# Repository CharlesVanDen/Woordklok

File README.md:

# Woordklok
Alternatieve besturing voor de woordklok van Samenkopen 2016
Dit project bestaat uit:
* een pcb met daarop een ATMEGA en andere elektronica
* een ESP01
* software voor de ATMEGA (Atmel Studio)
* software voor de ESP (Arduino)

Klik op Wiki (hierboven) voor meer informatie

CONTACT: Klik op Wiki (hierboven) en daarna op Bestellen

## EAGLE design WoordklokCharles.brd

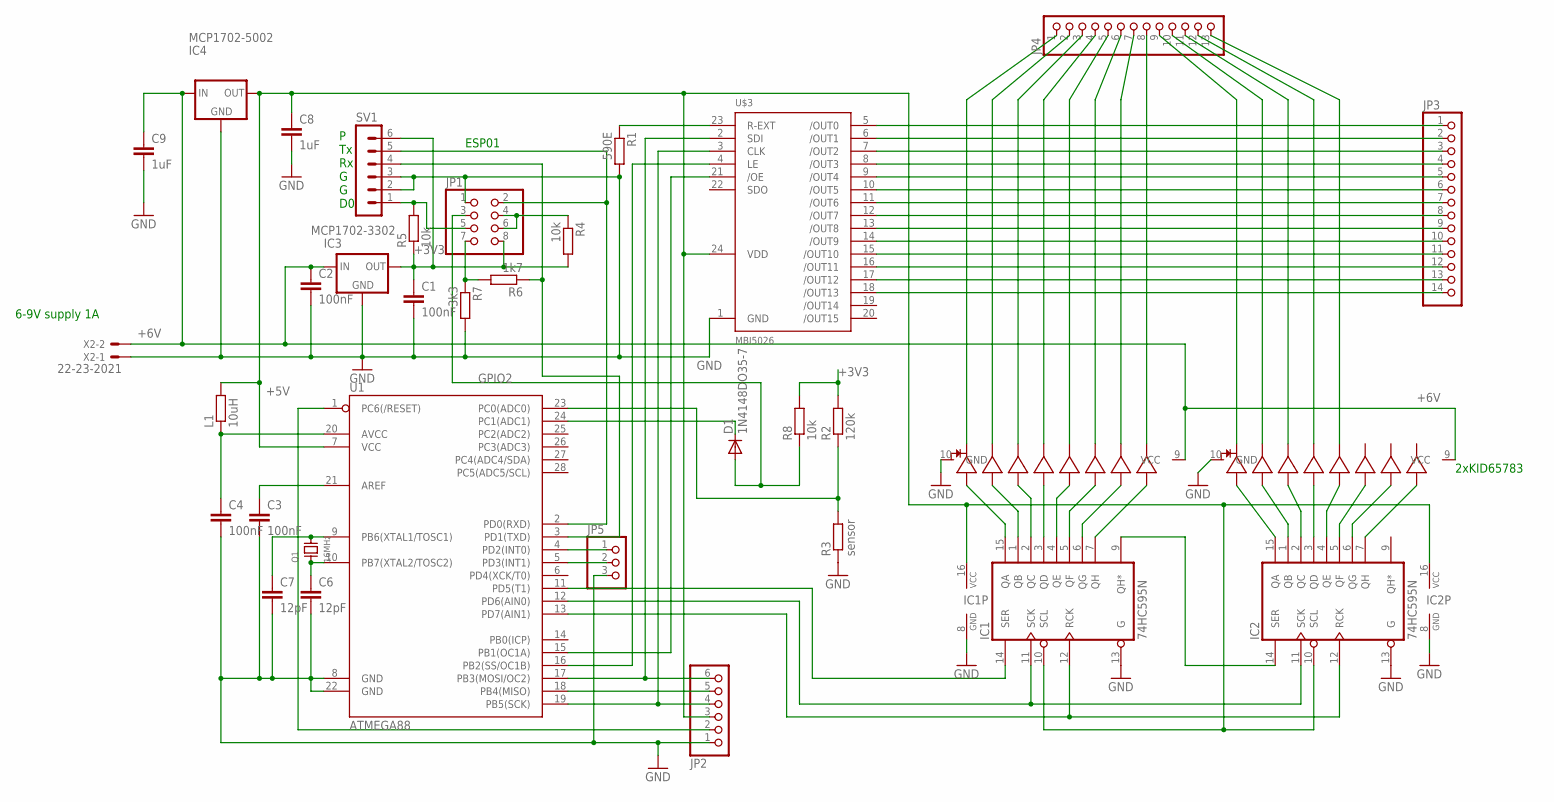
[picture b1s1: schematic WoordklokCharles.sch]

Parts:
C1, C2, C3, C4: 100nF; C025-024X044
C6, C7: 12pF; C025-024X044
C8, C9: 1uF; C025-024X044
D1: 1N4148DO35-7; DO35-7
IC1, IC2: 74HC595N; DIL16
IC3: MCP1702-3302; TO92
IC4: MCP1702-5002; TO92
JP1: PINHD-2X4; 2X04
JP2: PINHD-1X6; 1X06
JP3: PINHD-1X14; 1X14
JP4: PINHD-1X13; 1X13
JP5: PINHD-1X3; 1X03
L1: 10uH; 0204/7
Q1: 16MHz; XTAL
R1: 590E; 0204/7
R2: 120k; 0204/7
R3: sensor; 0204/7
R4, R5: 10k; 0204V
R6: 1k7; 0204/7
R7: 3k3; 0204/7
R8: 10k; 0204/7
SV1: MA06-1
U1: ATMEGA88; DIL28-3
U$1, U$2: KID65783; DIP18
U$3: MBI5026; DIP24
X2: 22-23-2021

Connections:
+3V3: C1.1, IC3.3 (OUT), JP1.8, R2.2, R4.2, R5.1, R8.2, SV1.6
+5V: C8.1, IC1.10 (SCL), IC1.16 (VCC), IC2.10 (SCL), IC2.16 (VCC), IC4.3 (OUT), JP2.3, L1.2, U1.7 (VCC), U$3.24 (VDD)
+6V: C2.1, C9.1, IC3.2 (IN), IC4.2 (IN), U$1.9 (VCC), U$2.9 (VCC), X2.2
AVCC: C4.1, L1.1, U1.20 (AVCC)
ESP2: JP1.2, SV1.5, U1.2 (PD0(RXD))
ESP7: R6.1, SV1.4, U1.3 (PD1(TXD))
GND: C1.2, C2.2, C3.2, C4.2, C6.2, C7.2, C8.2, C9.2, IC1.8 (GND), IC1.13 (G), IC2.8 (GND), IC2.13 (G), IC3.1 (GND), IC4.1 (GND), JP1.1, JP2.1, JP5.3, R1.2, R3.1, R7.2, SV1.2, SV1.3, U1.8 (GND), U1.22 (GND), U$1.10 (GND), U$2.10 (GND), U$3.1 (GND), X2.1
GPIO2: D1.A, JP1.3, R8.1
unnamed: IC1.15 (QA), U$1.8 (IN7)
unnamed: IC1.1 (QB), U$1.7 (IN6)
unnamed: IC1.2 (QC), U$1.6 (IN5)
unnamed: IC1.3 (QD), U$1.5 (IN4)
unnamed: IC1.4 (QE), U$1.4 (IN3)
unnamed: IC1.5 (QF), U$1.3 (IN2)
unnamed: IC1.6 (QG), U$1.2 (IN1)
unnamed: IC1.7 (QH), U$1.1 (IN0)
unnamed: IC2.15 (QA), U$2.8 (IN7)
unnamed: IC2.1 (QB), U$2.7 (IN6)
unnamed: IC2.2 (QC), U$2.6 (IN5)
unnamed: IC2.3 (QD), U$2.5 (IN4)
unnamed: IC2.4 (QE), U$2.4 (IN3)
unnamed: IC2.5 (QF), U$2.3 (IN2)
unnamed: IC2.6 (QG), U$2.2 (IN1)
unnamed: IC2.7 (QH), U$2.1 (IN0)
unnamed: IC1.9 (QH*), IC2.14 (SER)
unnamed: IC1.12 (RCK), IC2.12 (RCK), U1.13 (PD7(AIN1))
unnamed: IC1.11 (SCK), IC2.11 (SCK), U1.12 (PD6(AIN0))
unnamed: JP4.8, U$1.18 (OUT0)
unnamed: JP4.13, U$2.15 (OUT3)
unnamed: JP4.1, U$1.11 (OUT7)
unnamed: JP4.2, U$1.12 (OUT6)
unnamed: JP4.3, U$1.13 (OUT5)
unnamed: C3.1, U1.21 (AREF)
unnamed: JP3.2, U$3.6 (/OUT1)
unnamed: JP3.1, U$3.5 (/OUT0)
unnamed: R1.1, U$3.23 (R-EXT)
unnamed: JP1.5, R5.2, SV1.1
unnamed: JP1.4, JP1.6, R4.1
unnamed: JP2.4, U1.19 (PB5(SCK)), U$3.3 (CLK)
unnamed: JP2.6, U1.17 (PB3(MOSI/OC2)), U$3.2 (SDI)
unnamed: U1.16 (PB2(SS/OC1B)), U$3.4 (LE)
unnamed: IC1.14 (SER), U1.11 (PD5(T1))
unnamed: JP5.1, U1.4 (PD2(INT0))
unnamed: JP5.2, U1.5 (PD3(INT1))
unnamed: R2.1, R3.2, U1.23 (PC0(ADC0))
unnamed: JP2.5, U1.18 (PB4(MISO))
unnamed: JP2.2, U1.1 (PC6(/RESET))
unnamed: JP4.4, U$1.14 (OUT4)
unnamed: JP4.5, U$1.15 (OUT3)
unnamed: C7.1, Q1.P$2, U1.9 (PB6(XTAL1/TOSC1))
unnamed: C6.1, Q1.P$1, U1.10 (PB7(XTAL2/TOSC2))
unnamed: JP4.6, U$1.16 (OUT2)
unnamed: JP4.7, U$1.17 (OUT1)
unnamed: U1.15 (PB1(OC1A)), U$3.21 (/OE)
unnamed: JP4.9, U$2.11 (OUT7)
unnamed: JP4.10, U$2.12 (OUT6)
unnamed: JP4.11, U$2.13 (OUT5)
unnamed: JP4.12, U$2.14 (OUT4)
unnamed: JP3.14, U$3.18 (/OUT13)
unnamed: JP3.3, U$3.7 (/OUT2)
unnamed: JP3.4, U$3.8 (/OUT3)
unnamed: JP3.5, U$3.9 (/OUT4)
unnamed: JP3.6, U$3.10 (/OUT5)
unnamed: JP3.7, U$3.11 (/OUT6)
unnamed: JP3.8, U$3.12 (/OUT7)
unnamed: JP3.9, U$3.13 (/OUT8)
unnamed: JP3.10, U$3.14 (/OUT9)
unnamed: JP3.11, U$3.15 (/OUT10)
unnamed: JP3.12, U$3.16 (/OUT11)
unnamed: JP3.13, U$3.17 (/OUT12)
unnamed: JP1.7, R6.2, R7.1
unnamed: D1.C, U1.24 (PC1(ADC1))

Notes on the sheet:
2xKID65783
ESP01
P Tx Rx G G D0
6-9V supply 1A

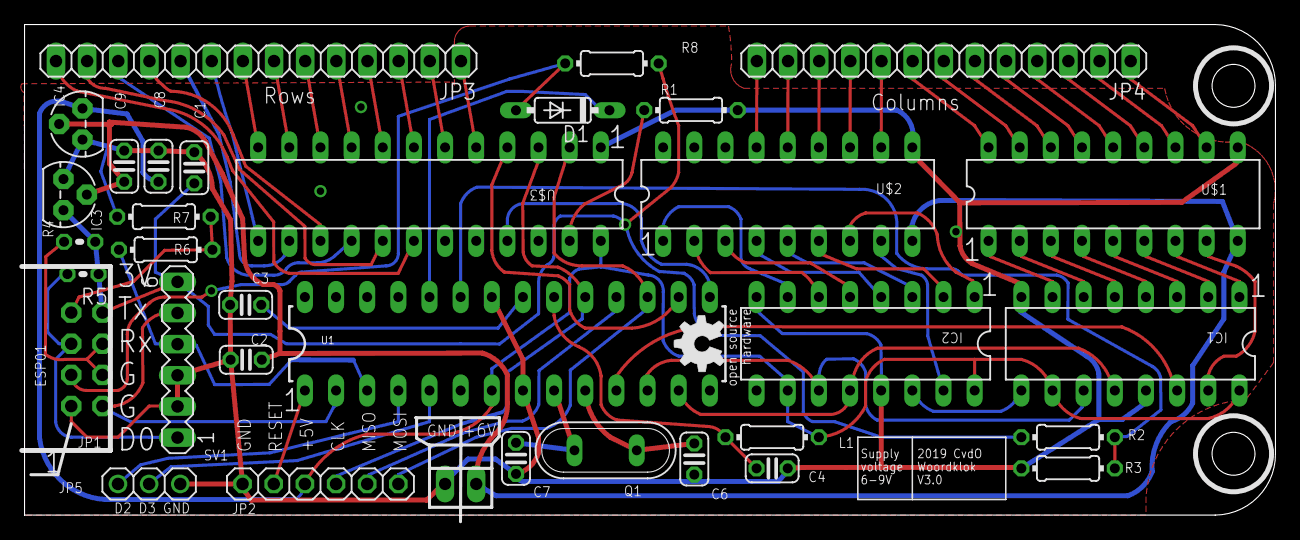
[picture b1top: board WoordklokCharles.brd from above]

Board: 2 copper layers, 102.0 x 40.0 mm, 35 parts (1 on the bottom side), 72 nets.

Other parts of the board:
U$4: OSHW_5MM

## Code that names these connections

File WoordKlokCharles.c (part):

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 
 connect:
 ATMEGA88 pin       MBI5026 pin (rows/cathodes of the leds)
 MOSI PB3 pin 17 to SDI pin 2
 SCK  PB5 pin 19 to CLK pin 3
 SS   PB2 pin 16 to LE  pin 4
      PB1 pin 15 to OE  pin 21
 ATMEGA88 pin       74HC595 pin (and then to KID65783 to the columns/anodes of leds)
 PD5                SDI pin 14
 PD6                CLK pin 11
 PD7                RCK pin 12

The MBI5026 is attached to the SPI pins of the ATMEGA, whereas the 74HC595's are done by software.
This is not a big deal as we clock one 1 into the 74HC595 and then shift that 1 through the shift register just 1 clock pulse at a time.
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}

int main(void){
	DDRB=0b00101110;//Set PB1 (OE), PB2 (latch), 3 (MOSI) and 5 (CLK) as output (rows of leds)
	DDRD=0b11100110;//set PD1 (TXD), 5 (data), 6 (clock) and 7 (latch) as output (columns of leds) and PD2 LED for debugging
	SPCR=(1<<SPE)|(1<<MSTR)|(1<<SPR0)|(1<<DORD);//Fspi=fcpu/128 |(1<<DORD) to send LSb first
	
	//setup 8-bit timer/counter 0 in CTC mode (mode 2), F=fcpu/64, 
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	print("Klok");
	
	
	//setup the ADC at 140kHz (16MHz/128), input is ADC0=PC0, reference is 1.1V
	//it is used for the Light Dependent Resistor (LDR) to determine ambient light level
	//when there is bright light, the LDR will have a low value and the voltage on ADC0 will be low (say, 0.4V)
	//when there is darkness, the LDR will have a high value and the voltage on ADC0 will be high (1.1V max)
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//As there are 13 columns, a complete screen takes 13ms
//makes a screen rate of 77 Hz, which is fine.
ISR(TIMER1_OVF_vect){
	//PIND|=(1<<2); //toggle PD2, just for debugging
	static 	uint8_t column=0;

	SPDR=pixels[column]&0xff;//send LSB
	while(!(SPSR & (1<<SPIF))) {}//wait for transfer to complete
	SPDR=pixels[column]>>8;//send MSB
	while(!(SPSR & (1<<SPIF))) {}//wait for transfer to complete
	//PORTB|= (1<<1);//output disable on the MBI5026 on PB1; this is now done in hardware (PWM output OC1A)
	delay_ms(1);
	PORTD|= (1<<6); //clock for columns
	PORTB|= (1<<2);//latch for rows
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	PORTB&=~(1<<2);
	PORTD&=~(1<<6);
	PORTD&=~(1<<7);
	//PORTB&=~(1<<1);//output enable on the MBI5026 on PB1; this is now done in hardware (PWM output OC1A)
	
	column=(column+1)%NUM_COLUMNS;
	if(column==0)PORTD|=(1<<5); //PD5 on
	else PORTD&=~(1<<5);
}

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
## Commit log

2018-06-21 Werkende versie zonder animaties
2018-06-21 Versie met animatie lopende letters
    Bug rond 1 uur gefixt
2018-07-09 Bug in de definitie van het woord EEN gecorrigeerd
2018-07-31 GNU GPL3
2018-07-31 CADSoft Eagle pcb design files for version 1 of the pcb
2018-07-31 Image of the unpopulated pcb
2018-07-31 create directory img
2018-07-31 Photo of the unpopulated printed circuit board (pcb)
2018-07-31 Photo of the pcb populated and installed in the Woordklok
2018-07-31 Schema hoe de LEDs aan te sluiten
2018-07-31 Electronic schematic diagram
2018-08-01 ESP01 adapter
2018-11-10 Three images added
2018-12-30 2.0 versie van de woordklok
2019-02-02 V3.0 of CADsoft Eagle files,
    V3.0: changed IC3 to MCP1702-33
    V2.0: added pull-up resistors for ESP01, several minor corrections
2020-08-23 Fixed problem with zero NTP leading to 07:28
    Issue: If the 32-bit time value in the NTP packet contains all zeroes, this is interpreted as 2036-02-07T06:28:18Z. Therefore, the clock is set to the wrong time (to 7:28 in CET).
    In applications where a wake up call is used, if it is set to 7:30, the alarm will go off after two minutes, which is annoying.
    Solution: check for the time value being 0. If so, ignore it.
2020-08-23 Delete ESP01.ino
    This file is replaced by ESP01WifiManager
2022-02-28 Originele handleiding v.d. mechanische opbouw 2016
    Omdat de oorspronkelijke handleiding op de website http://wordclock_old.protoart.net niet meer te vinden is, voor degenen die na al die jaren nog steeds de doos ongeopend op zolder hebben staan, hier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
2026-04-18 screenshot of the woordklok home page
2026-04-18 screenshot ziggo modem

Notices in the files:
parts and their libraries:
SparkFun-DigitalIC: Licensing: Creative Commons ShareAlike 4.0 International - https://creativecommons.org/licenses/by-sa/4.0
